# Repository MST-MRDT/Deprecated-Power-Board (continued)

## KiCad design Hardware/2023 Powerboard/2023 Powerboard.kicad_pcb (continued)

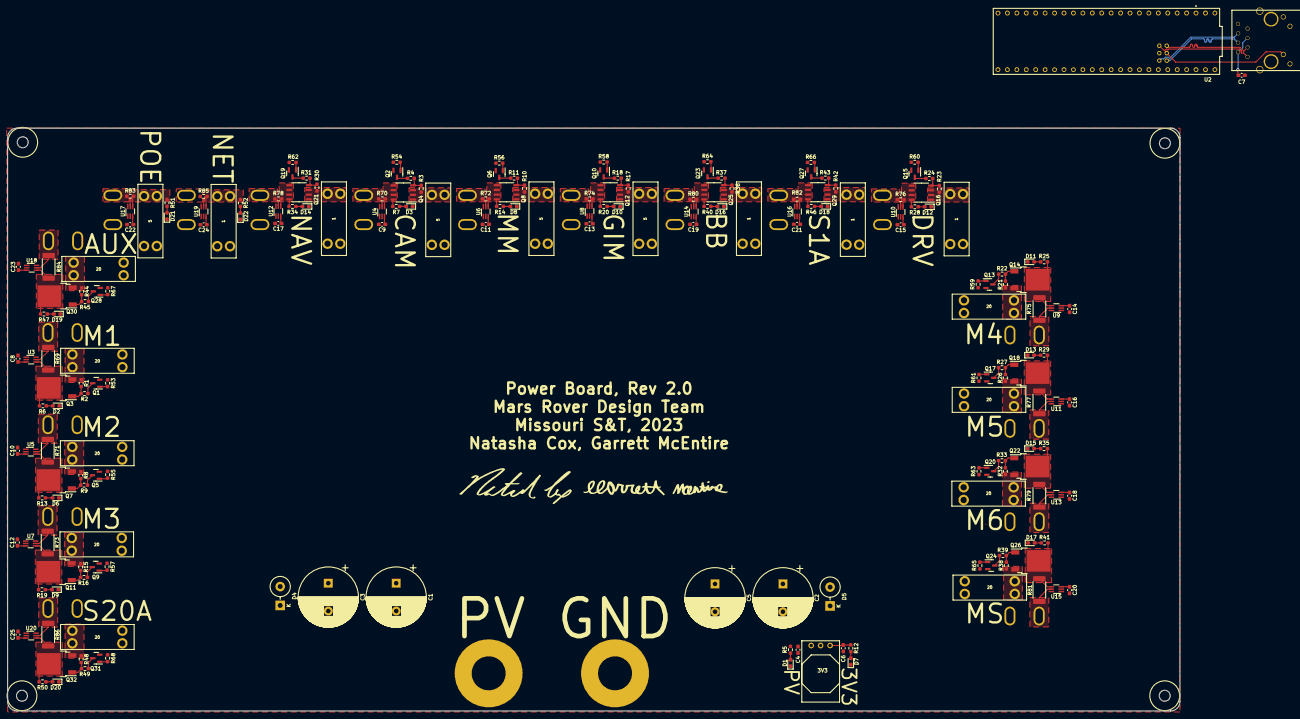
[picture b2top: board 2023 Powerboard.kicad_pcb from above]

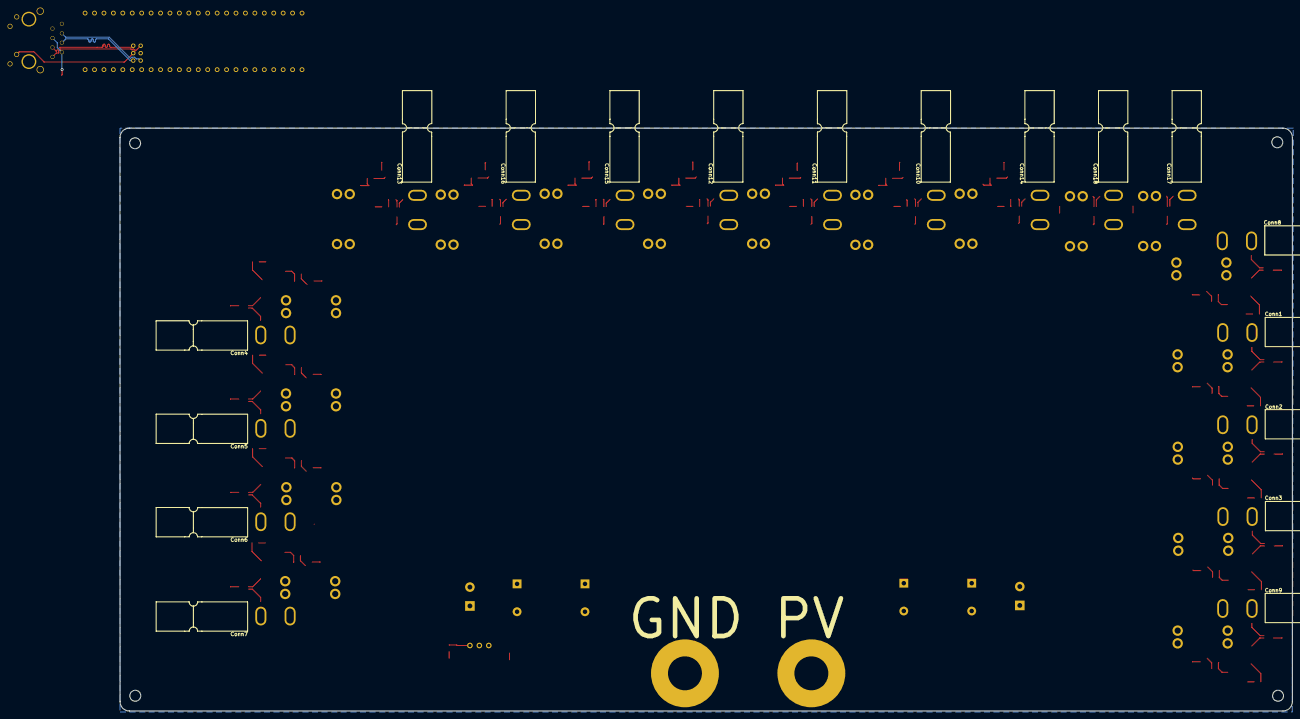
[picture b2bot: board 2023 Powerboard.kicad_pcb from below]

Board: 4 copper layers, 315.7 x 157.0 mm, 228 parts (18 on the bottom side), 147 nets.

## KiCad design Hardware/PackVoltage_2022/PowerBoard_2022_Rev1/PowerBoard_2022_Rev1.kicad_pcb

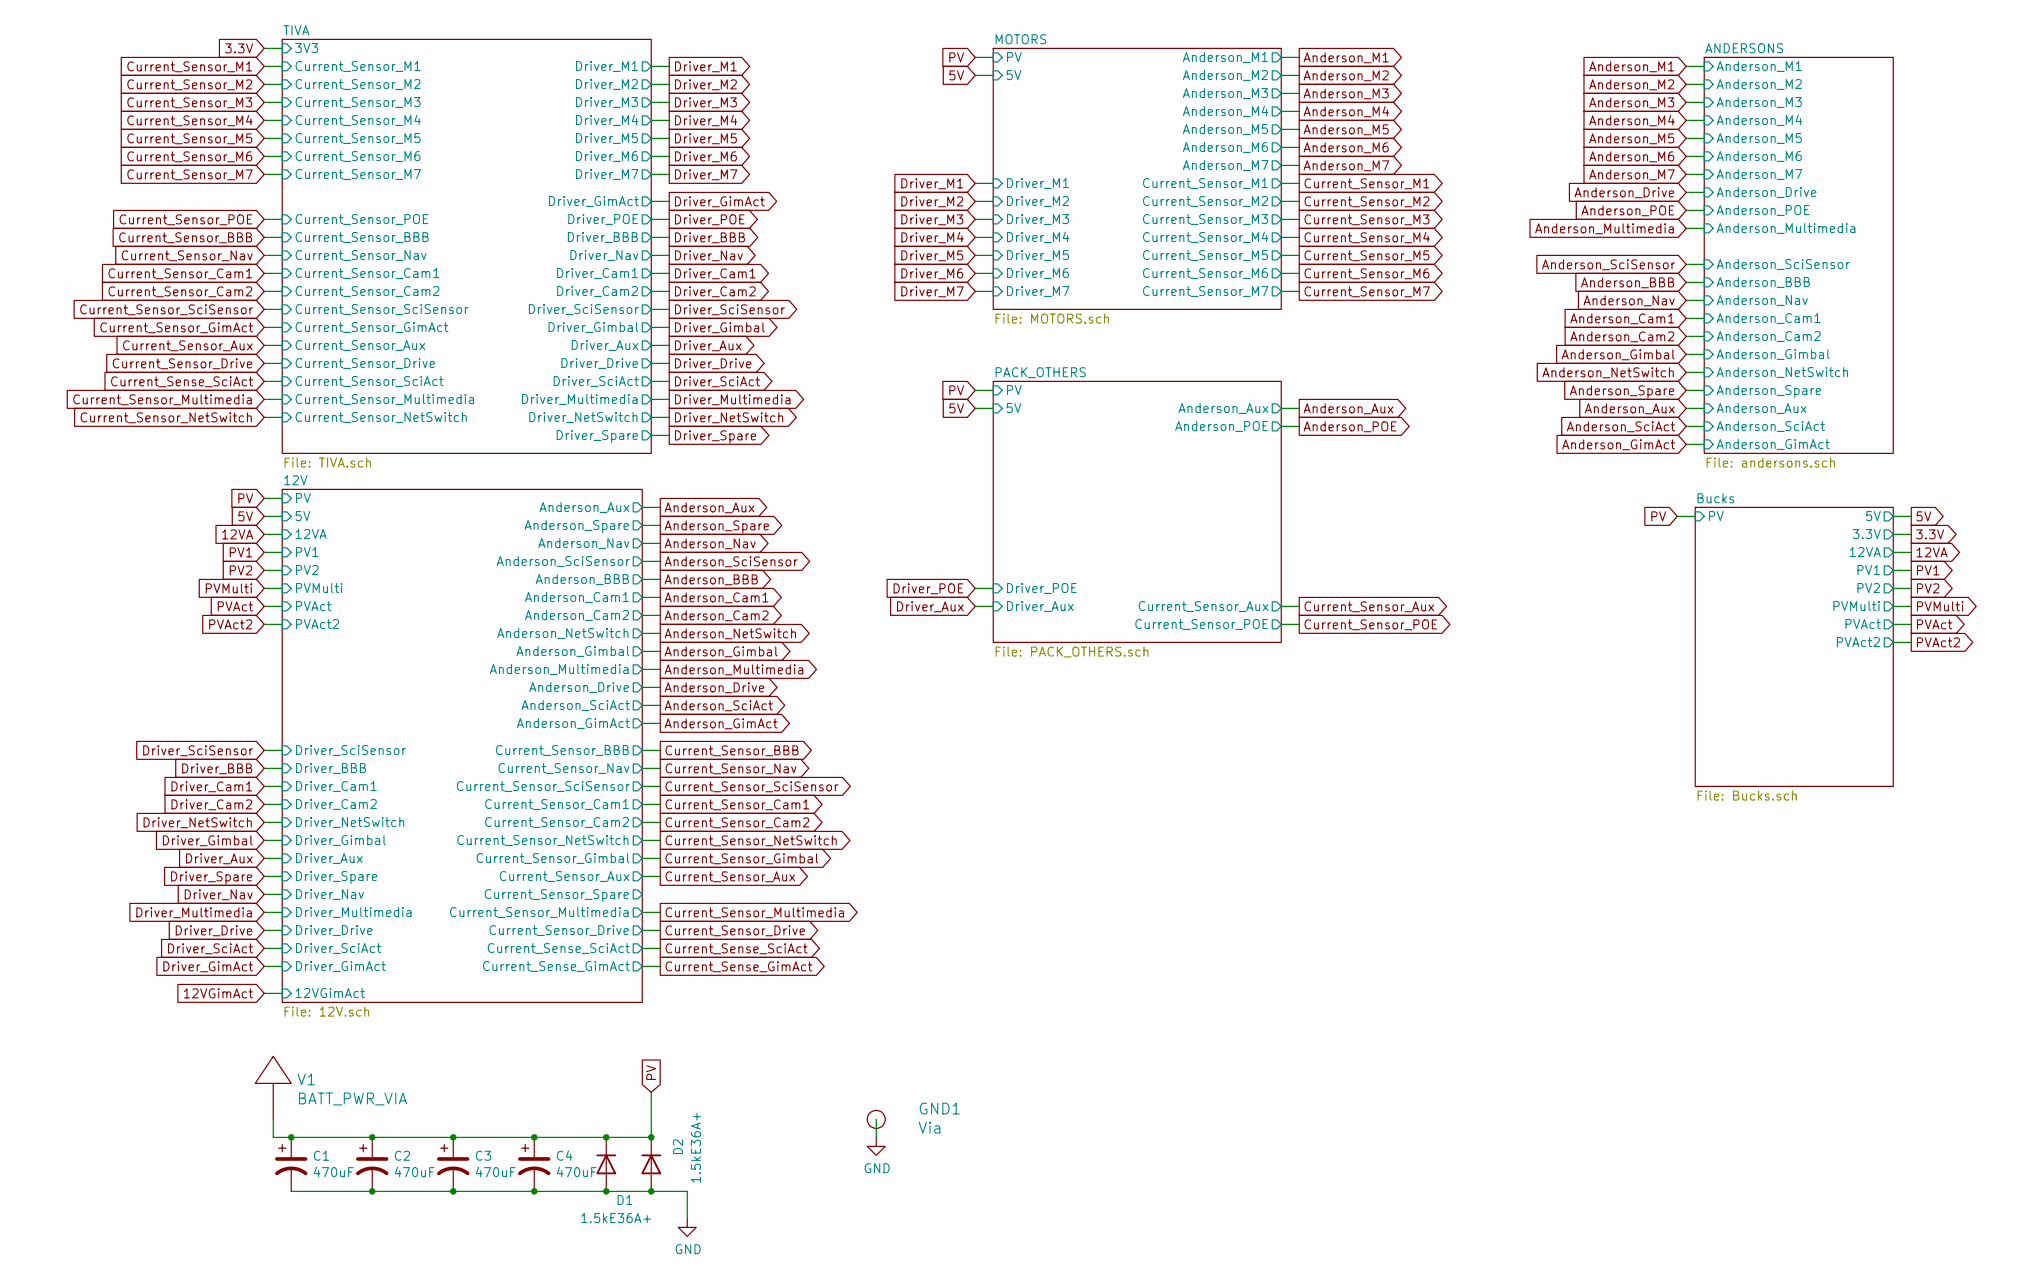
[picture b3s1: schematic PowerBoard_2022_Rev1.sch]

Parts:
C1, C2, C3, C4: 470uF; CP_Radial_D12.5mm_P5.00mm
D1, D2: 1.5kE36A+; D_DO-201_P5.08mm_Vertical_KathodeUp
GND1: Via; BATT_PWR_VIA
V1: BATT_PWR_VIA

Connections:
GND: C1.2, C2.2, C3.2, C4.2, D1.2 (A), D2.2 (A), GND1.1; also elsewhere on the board
PV: C1.1, C2.1, C3.1, C4.1, D1.1 (K), D2.1 (K), V1.1; also elsewhere on the board

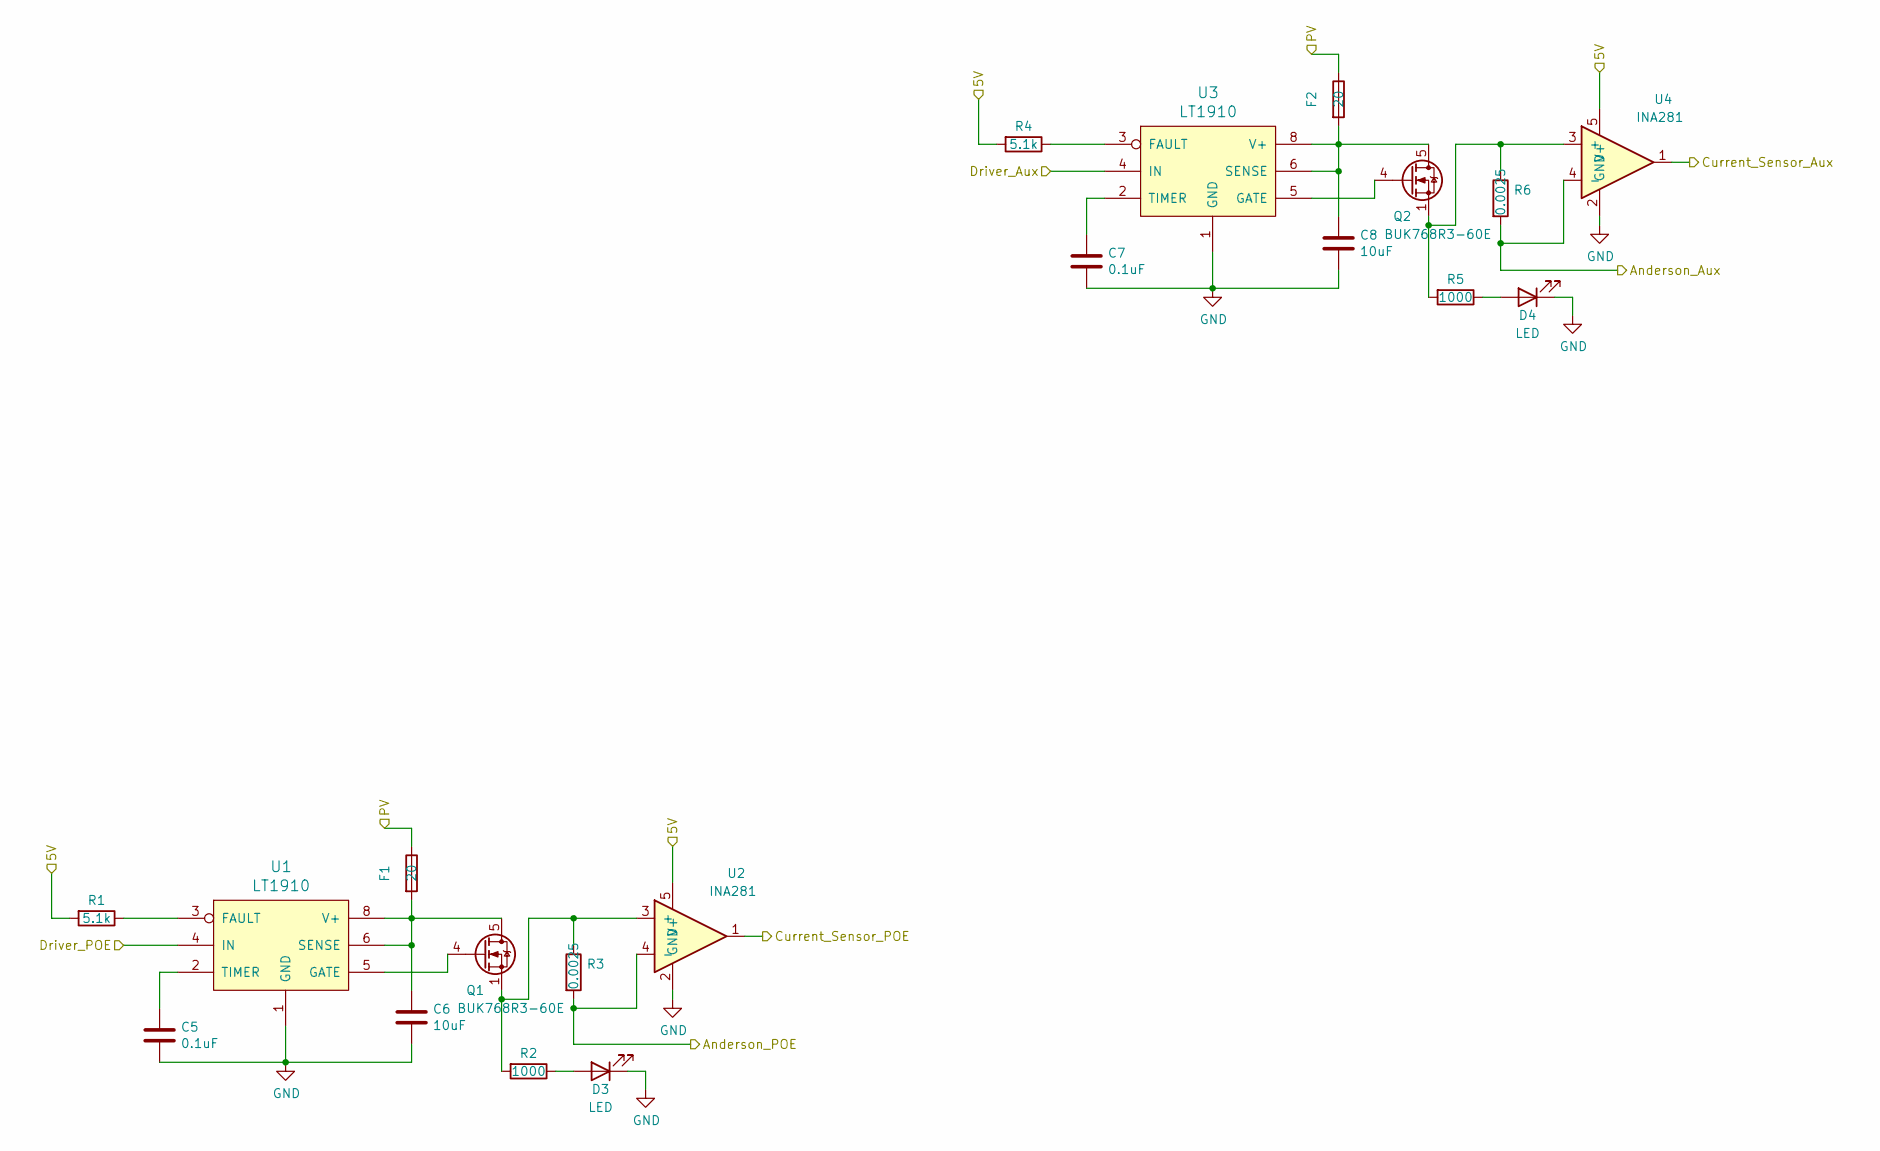
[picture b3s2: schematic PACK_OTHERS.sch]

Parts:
C5, C7: 0.1uF; C_0603_1608Metric_Pad1.05x0.95mm_HandSolder
C6, C8: 10uF; C_0603_1608Metric_Pad1.05x0.95mm_HandSolder
D3, D4: LED; LED_0603_1608Metric_Pad1.05x0.95mm_HandSolder
F1, F2: 20; ATC_Fuse_Block
Q1, Q2: BUK768R3-60E; LFPAK33
R1, R4: 5.1k; R_0603_1608Metric_Pad1.05x0.95mm_HandSolder
R2, R5: 1000; R_0603_1608Metric_Pad1.05x0.95mm_HandSolder
R3, R6: 0.0025; R_0402_1005Metric_Pad0.72x0.64mm_HandSolder
U1, U3: LT1910; SOIC-8_3.9x4.9mm_P1.27mm
U2, U4: INA281; SOT-23-5

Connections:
5V: R1.2, R4.2, U2.5 (V+), U4.5 (V+); also elsewhere on the board
Anderson_Aux: R6.2, U4.4 (-); also elsewhere on the board
Anderson_POE: R3.2, U2.4 (-); also elsewhere on the board
Current_Sensor_Aux: U4.1; also elsewhere on the board
Current_Sensor_POE: U2.1; also elsewhere on the board
Driver_Aux: U3.4 (IN); also elsewhere on the board
Driver_POE: U1.4 (IN); also elsewhere on the board
GND: C5.2, C6.2, C7.2, C8.2, D3.1 (K), D4.1 (K), U1.1 (GND), U2.2 (GND), U3.1 (GND), U4.2 (GND); also elsewhere on the board
unnamed: C5.1, U1.2 (TIMER)
unnamed: C6.1, F1.2, Q1.5 (D), U1.6 (SENSE), U1.8 (V+)
unnamed: C7.1, U3.2 (TIMER)
unnamed: C8.1, F2.2, Q2.5 (D), U3.6 (SENSE), U3.8 (V+)
unnamed: D3.2 (A), R2.1
unnamed: D4.2 (A), R5.1
unnamed: Q1.1 (S), Q1.2 (S), Q1.3 (S), R2.2, R3.1, U2.3 (+)
unnamed: Q1.4 (G), U1.5 (GATE)
unnamed: Q2.1 (S), Q2.2 (S), Q2.3 (S), R5.2, R6.1, U4.3 (+)
unnamed: Q2.4 (G), U3.5 (GATE)
unnamed: R1.1, U1.3 (FAULT)
unnamed: R4.1, U3.3 (FAULT)
PV: F1.1, F2.1; also elsewhere on the board

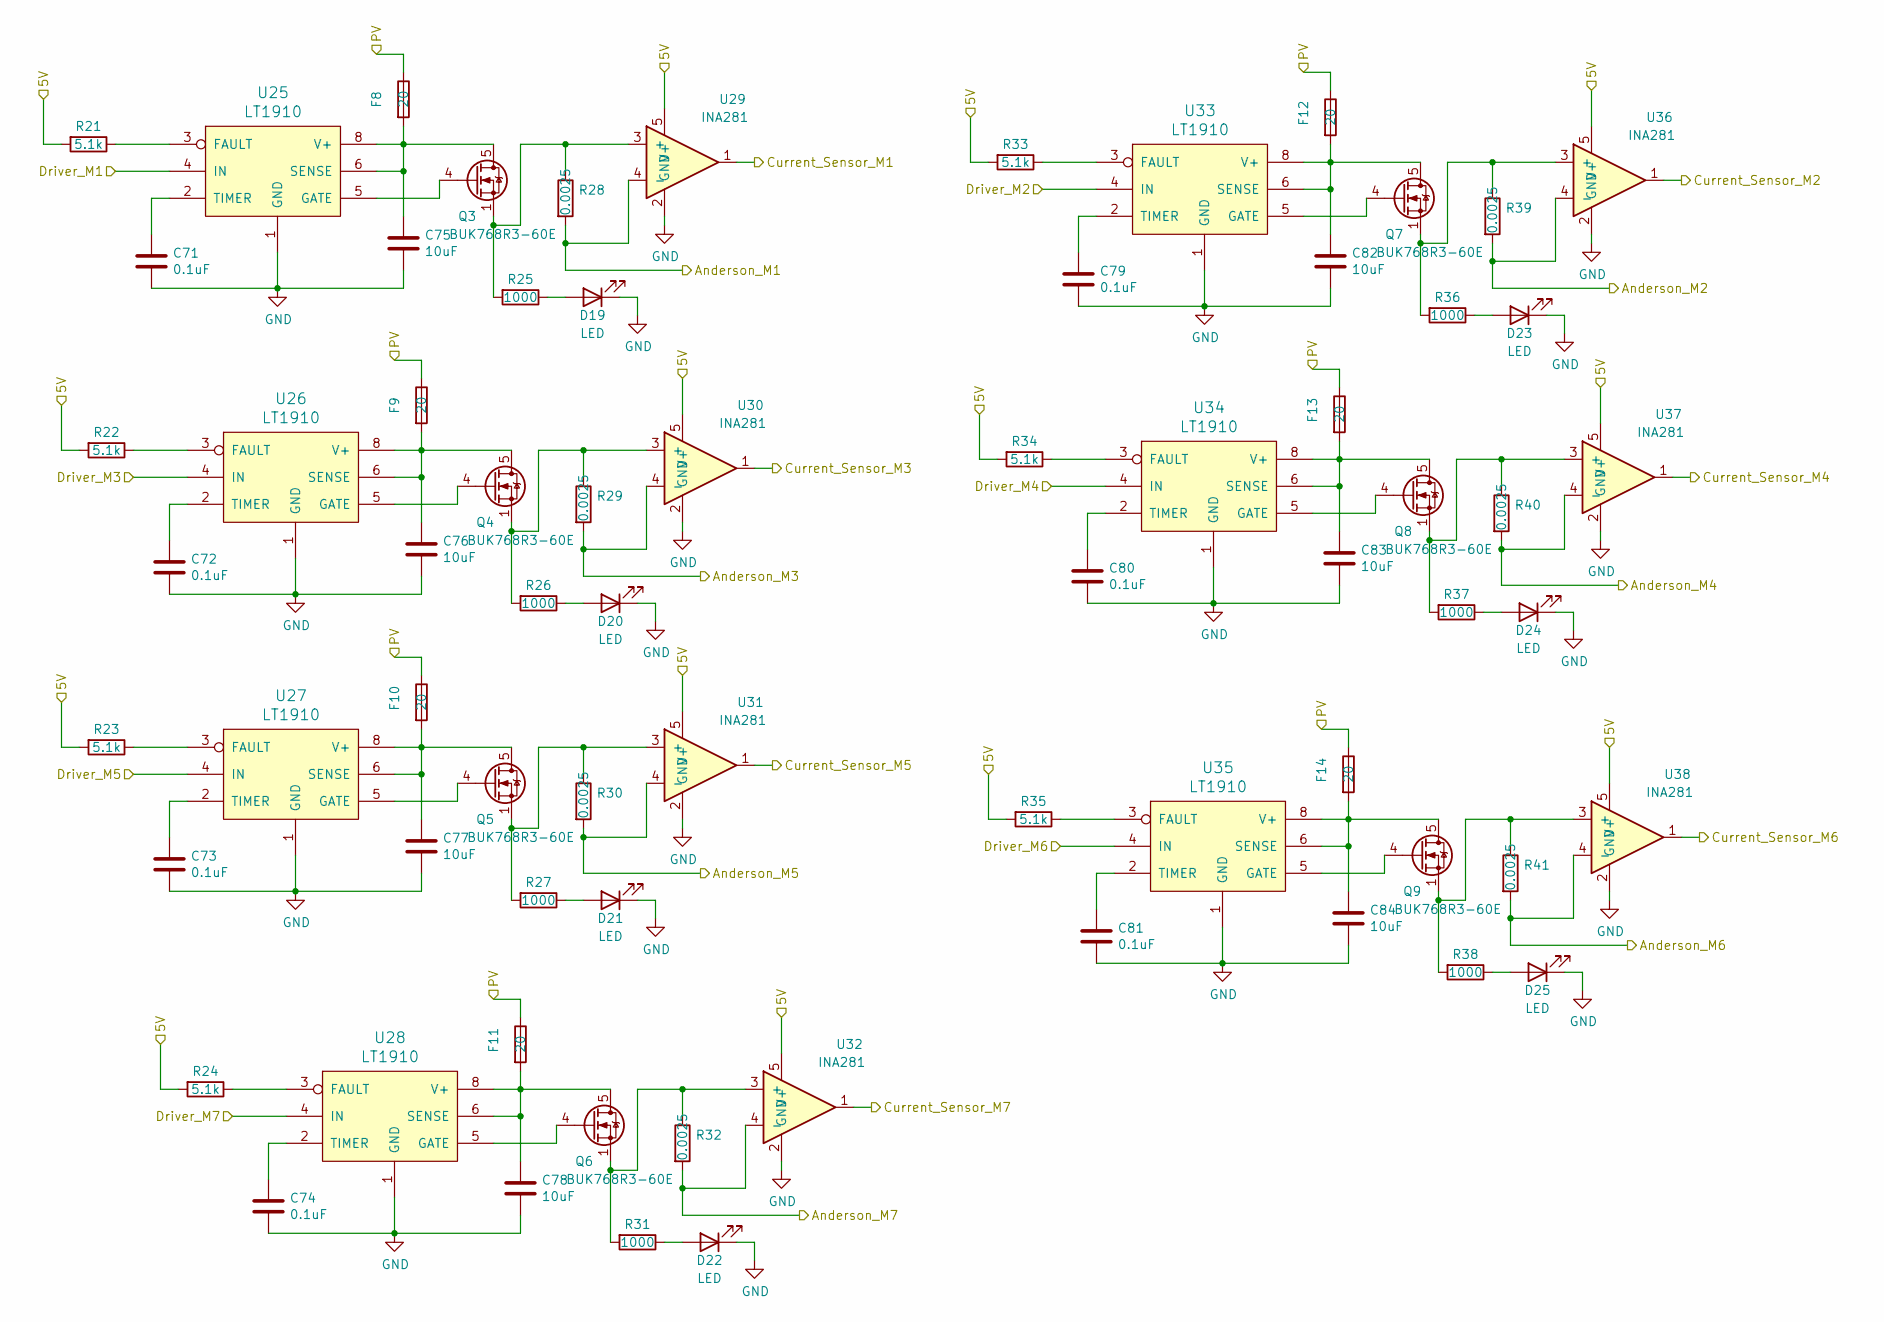
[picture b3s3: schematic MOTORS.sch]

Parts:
C71, C72, C73, C74, C79, C80, C81: 0.1uF; C_0603_1608Metric_Pad1.05x0.95mm_HandSolder
C75, C76, C77, C78, C82, C83, C84: 10uF; C_0603_1608Metric_Pad1.05x0.95mm_HandSolder
D19, D20, D21, D22, D23, D24, D25: LED; LED_0603_1608Metric_Pad1.05x0.95mm_HandSolder
F8, F9, F10, F11, F12, F13, F14: 20; ATC_Fuse_Block
Q3, Q4, Q5, Q6, Q7, Q8, Q9: BUK768R3-60E; LFPAK33
R21, R22, R23, R24, R33, R34, R35: 5.1k; R_0603_1608Metric_Pad1.05x0.95mm_HandSolder
R25, R26, R27, R31, R36, R37, R38: 1000; R_0603_1608Metric_Pad1.05x0.95mm_HandSolder
R28, R29, R30, R32, R39, R40, R41: 0.0025; R_0402_1005Metric_Pad0.72x0.64mm_HandSolder
U25, U26, U27, U28, U33, U34, U35: LT1910; SOIC-8_3.9x4.9mm_P1.27mm
U29, U30, U31, U32, U36, U37, U38: INA281; SOT-23-5

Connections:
5V: R21.2, R22.2, R23.2, R24.2, R33.2, R34.2, R35.2, U29.5 (V+), U30.5 (V+), U31.5 (V+), U32.5 (V+), U36.5 (V+), U37.5 (V+), U38.5 (V+); also elsewhere on the board
Anderson_M1: R28.2, U29.4 (-); also elsewhere on the board
Anderson_M2: R39.2, U36.4 (-); also elsewhere on the board
Anderson_M3: R29.2, U30.4 (-); also elsewhere on the board
Anderson_M4: R40.2, U37.4 (-); also elsewhere on the board
Anderson_M5: R30.2, U31.4 (-); also elsewhere on the board
Anderson_M6: R41.2, U38.4 (-); also elsewhere on the board
Anderson_M7: R32.2, U32.4 (-); also elsewhere on the board
Current_Sensor_M1: U29.1; also elsewhere on the board
Current_Sensor_M2: U36.1; also elsewhere on the board
Current_Sensor_M3: U30.1; also elsewhere on the board
Current_Sensor_M4: U37.1; also elsewhere on the board
Current_Sensor_M5: U31.1; also elsewhere on the board
Current_Sensor_M6: U38.1; also elsewhere on the board
Current_Sensor_M7: U32.1; also elsewhere on the board
Driver_M1: U25.4 (IN); also elsewhere on the board
Driver_M2: U33.4 (IN); also elsewhere on the board
Driver_M3: U26.4 (IN); also elsewhere on the board
Driver_M4: U34.4 (IN); also elsewhere on the board
Driver_M5: U27.4 (IN); also elsewhere on the board
Driver_M6: U35.4 (IN); also elsewhere on the board
Driver_M7: U28.4 (IN); also elsewhere on the board
GND: C71.2, C72.2, C73.2, C74.2, C75.2, C76.2, C77.2, C78.2, C79.2, C80.2, C81.2, C82.2, C83.2, C84.2, D19.1 (K), D20.1 (K), D21.1 (K), D22.1 (K), D23.1 (K), D24.1 (K), D25.1 (K), U25.1 (GND), U26.1 (GND), U27.1 (GND), U28.1 (GND), U29.2 (GND), U30.2 (GND), U31.2 (GND), U32.2 (GND), U33.1 (GND), U34.1 (GND), U35.1 (GND), U36.2 (GND), U37.2 (GND), U38.2 (GND); also elsewhere on the board
unnamed: C71.1, U25.2 (TIMER)
unnamed: C72.1, U26.2 (TIMER)
unnamed: C73.1, U27.2 (TIMER)
unnamed: C74.1, U28.2 (TIMER)
unnamed: C75.1, F8.2, Q3.5 (D), U25.6 (SENSE), U25.8 (V+)
unnamed: C76.1, F9.2, Q4.5 (D), U26.6 (SENSE), U26.8 (V+)
unnamed: C77.1, F10.2, Q5.5 (D), U27.6 (SENSE), U27.8 (V+)
unnamed: C78.1, F11.2, Q6.5 (D), U28.6 (SENSE), U28.8 (V+)
unnamed: C79.1, U33.2 (TIMER)
unnamed: C80.1, U34.2 (TIMER)
unnamed: C81.1, U35.2 (TIMER)
unnamed: C82.1, F12.2, Q7.5 (D), U33.6 (SENSE), U33.8 (V+)
unnamed: C83.1, F13.2, Q8.5 (D), U34.6 (SENSE), U34.8 (V+)
unnamed: C84.1, F14.2, Q9.5 (D), U35.6 (SENSE), U35.8 (V+)
unnamed: D19.2 (A), R25.1
unnamed: D20.2 (A), R26.1
unnamed: D21.2 (A), R27.1
unnamed: D22.2 (A), R31.1
unnamed: D23.2 (A), R36.1
unnamed: D24.2 (A), R37.1
unnamed: D25.2 (A), R38.1
unnamed: Q3.1 (S), Q3.2 (S), Q3.3 (S), R25.2, R28.1, U29.3 (+)
unnamed: Q3.4 (G), U25.5 (GATE)
unnamed: Q4.1 (S), Q4.2 (S), Q4.3 (S), R26.2, R29.1, U30.3 (+)
unnamed: Q4.4 (G), U26.5 (GATE)
unnamed: Q5.1 (S), Q5.2 (S), Q5.3 (S), R27.2, R30.1, U31.3 (+)
unnamed: Q5.4 (G), U27.5 (GATE)
unnamed: Q6.1 (S), Q6.2 (S), Q6.3 (S), R31.2, R32.1, U32.3 (+)
unnamed: Q6.4 (G), U28.5 (GATE)
unnamed: Q7.1 (S), Q7.2 (S), Q7.3 (S), R36.2, R39.1, U36.3 (+)
unnamed: Q7.4 (G), U33.5 (GATE)
unnamed: Q8.1 (S), Q8.2 (S), Q8.3 (S), R37.2, R40.1, U37.3 (+)
unnamed: Q8.4 (G), U34.5 (GATE)
unnamed: Q9.1 (S), Q9.2 (S), Q9.3 (S), R38.2, R41.1, U38.3 (+)
unnamed: Q9.4 (G), U35.5 (GATE)
unnamed: R21.1, U25.3 (FAULT)
unnamed: R22.1, U26.3 (FAULT)
unnamed: R23.1, U27.3 (FAULT)
unnamed: R24.1, U28.3 (FAULT)
unnamed: R33.1, U33.3 (FAULT)
unnamed: R34.1, U34.3 (FAULT)
unnamed: R35.1, U35.3 (FAULT)
PV: F8.1, F9.1, F10.1, F11.1, F12.1, F13.1, F14.1; also elsewhere on the board

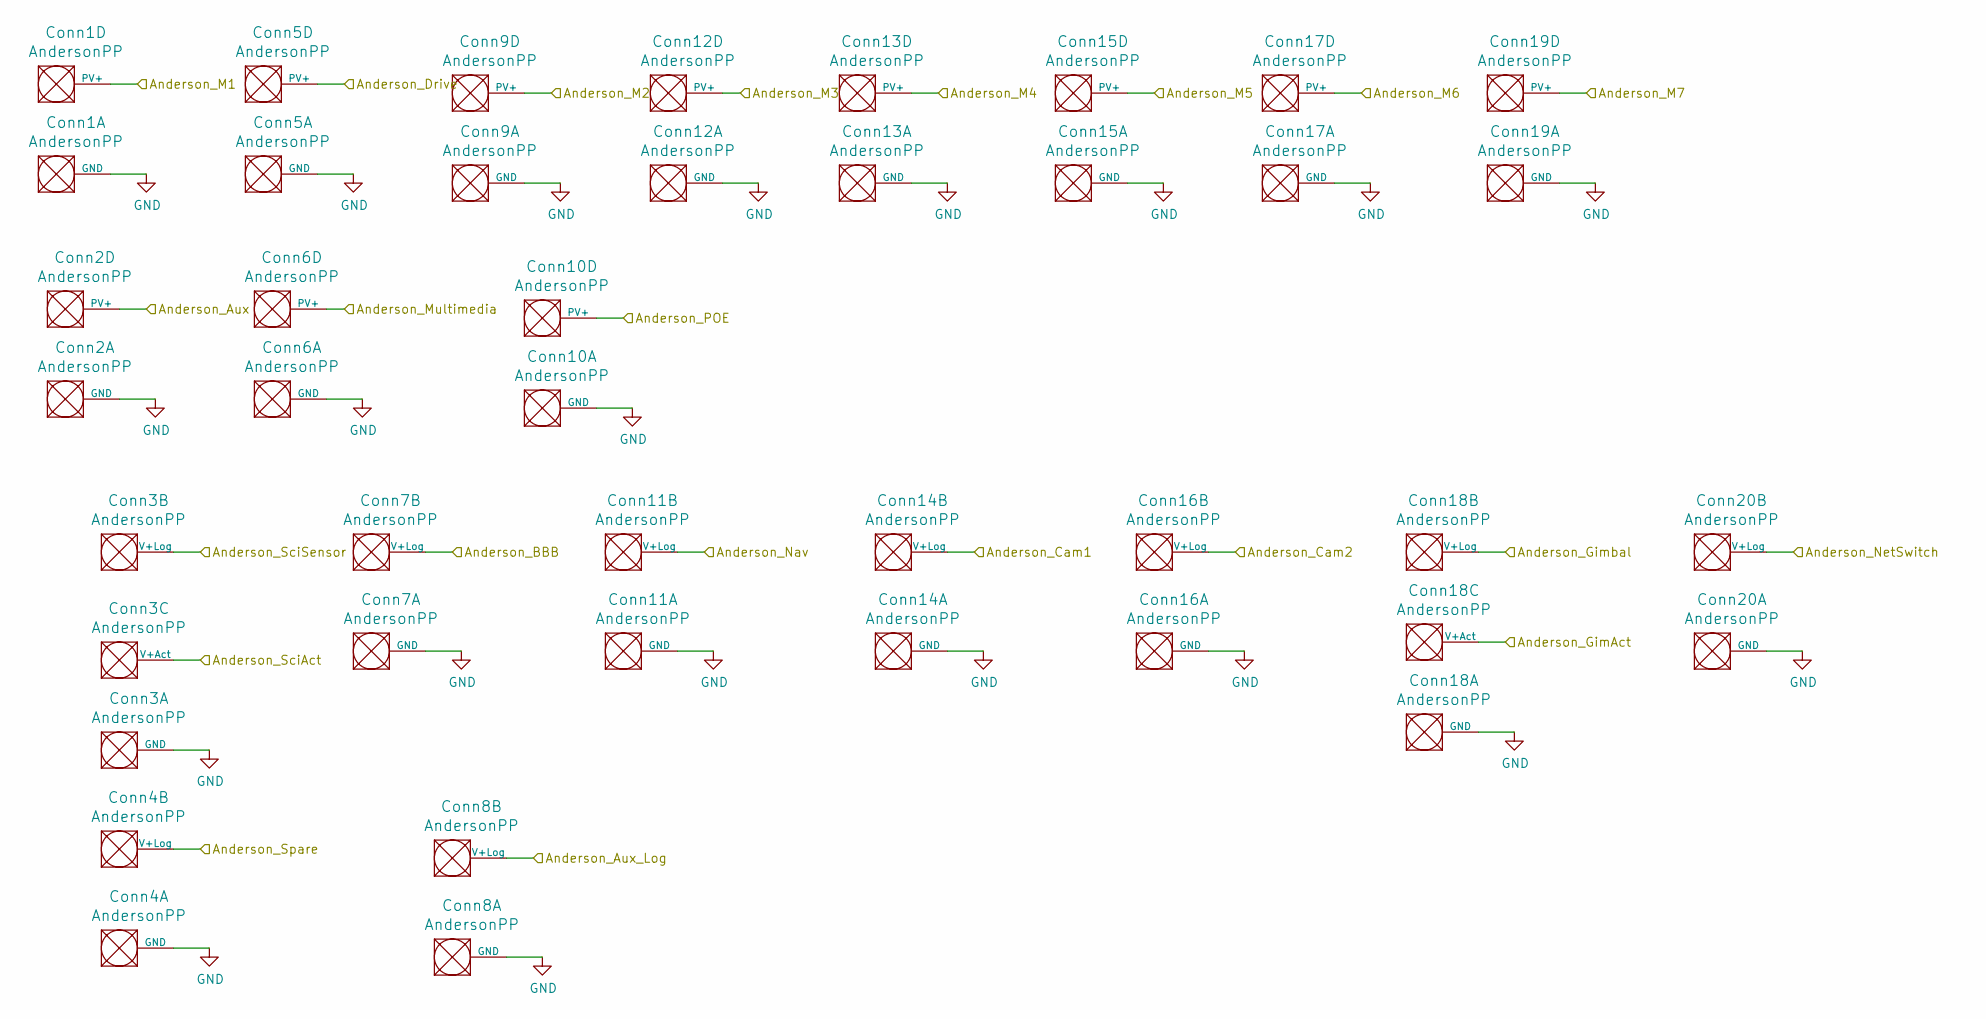
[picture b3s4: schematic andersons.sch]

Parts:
Conn1, Conn2, Conn5, Conn6, Conn9, Conn10, Conn12, Conn13, Conn15, Conn17, Conn19: AndersonPP; Anderson_2_Vertical_Side_by_Side_PV
Conn3, Conn18: AndersonPP; Anderson_3_Vertical_Side_by_Side
Conn4, Conn7, Conn8, Conn11, Conn14, Conn16, Conn20: AndersonPP; Anderson_2_Vertical_Sidy_by_Side

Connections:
Anderson_Aux: Conn2.4 (PV+); also elsewhere on the board
Anderson_Aux_Logic: Conn8.2 (V+Log); also elsewhere on the board
Anderson_BBB: Conn7.2 (V+Log); also elsewhere on the board
Anderson_Cam1: Conn14.2 (V+Log); also elsewhere on the board
Anderson_Cam2: Conn16.2 (V+Log); also elsewhere on the board
Anderson_Drive: Conn5.4 (PV+); also elsewhere on the board
Anderson_GimAct: Conn18.3 (V+Act); also elsewhere on the board
Anderson_Gimbal: Conn18.2 (V+Log); also elsewhere on the board
Anderson_M1: Conn1.4 (PV+); also elsewhere on the board
Anderson_M2: Conn9.4 (PV+); also elsewhere on the board
Anderson_M3: Conn12.4 (PV+); also elsewhere on the board
Anderson_M4: Conn13.4 (PV+); also elsewhere on the board
Anderson_M5: Conn15.4 (PV+); also elsewhere on the board
Anderson_M6: Conn17.4 (PV+); also elsewhere on the board
Anderson_M7: Conn19.4 (PV+); also elsewhere on the board
Anderson_Multimedia: Conn6.4 (PV+); also elsewhere on the board
Anderson_Nav: Conn11.2 (V+Log); also elsewhere on the board
Anderson_NetSwitch: Conn20.2 (V+Log); also elsewhere on the board
Anderson_POE: Conn10.4 (PV+); also elsewhere on the board
Anderson_SciAct: Conn3.3 (V+Act); also elsewhere on the board
Anderson_SciSensor: Conn3.2 (V+Log); also elsewhere on the board
Anderson_Spare: Conn4.2 (V+Log); also elsewhere on the board
GND: Conn1.1 (GND), Conn2.1 (GND), Conn3.1 (GND), Conn4.1 (GND), Conn5.1 (GND), Conn6.1 (GND), Conn7.1 (GND), Conn8.1 (GND), Conn9.1 (GND), Conn10.1 (GND), Conn11.1 (GND), Conn12.1 (GND), Conn13.1 (GND), Conn14.1 (GND), Conn15.1 (GND), Conn16.1 (GND), Conn17.1 (GND), Conn18.1 (GND), Conn19.1 (GND), Conn20.1 (GND); also elsewhere on the board

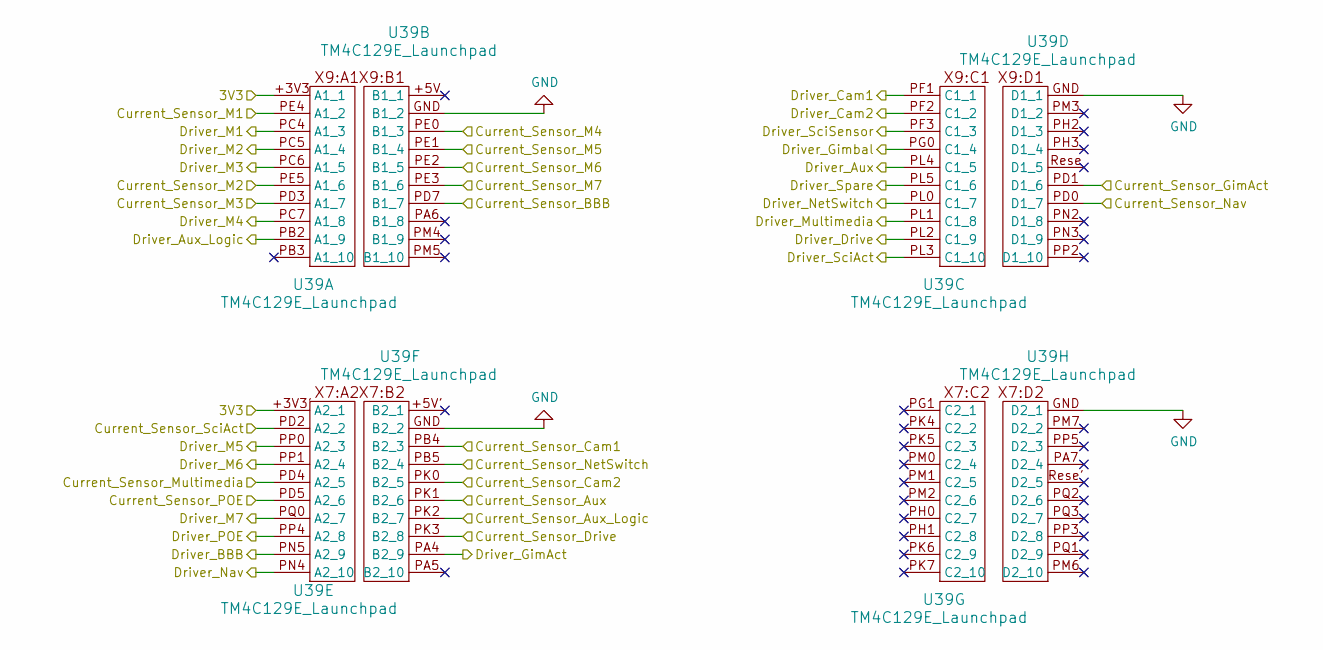
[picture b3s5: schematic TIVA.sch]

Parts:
U39: TM4C129E_Launchpad; TM4C129E_Launchpad_FULL_THT_TOP

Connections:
3.3V: U39.+3V3 (A1_1), U39.+3V3' (A2_1); also elsewhere on the board
Current_Sensor_Aux: U39.PK1 (B2_6); also elsewhere on the board
Current_Sensor_Aux_Logic: U39.PK2 (B2_7); also elsewhere on the board
Current_Sensor_BBB: U39.PD7 (B1_7); also elsewhere on the board
Current_Sensor_Cam1: U39.PB4 (B2_3); also elsewhere on the board
Current_Sensor_Cam2: U39.PK0 (B2_5); also elsewhere on the board
Current_Sensor_Drive: U39.PK3 (B2_8); also elsewhere on the board
Current_Sensor_GimAct: U39.PD1 (D1_6); also elsewhere on the board
Current_Sensor_M1: U39.PE4 (A1_2); also elsewhere on the board
Current_Sensor_M2: U39.PE5 (A1_6); also elsewhere on the board
Current_Sensor_M3: U39.PD3 (A1_7); also elsewhere on the board
Current_Sensor_M4: U39.PE0 (B1_3); also elsewhere on the board
Current_Sensor_M5: U39.PE1 (B1_4); also elsewhere on the board
Current_Sensor_M6: U39.PE2 (B1_5); also elsewhere on the board
Current_Sensor_M7: U39.PE3 (B1_6); also elsewhere on the board
Current_Sensor_Multimedia: U39.PD4 (A2_5); also elsewhere on the board
Current_Sensor_Nav: U39.PD0 (D1_7); also elsewhere on the board
Current_Sensor_NetSwitch: U39.PB5 (B2_4); also elsewhere on the board
Current_Sensor_POE: U39.PD5 (A2_6); also elsewhere on the board
Current_Sensor_SciAct: U39.PD2 (A2_2); also elsewhere on the board
Driver_Aux: U39.PL4 (C1_5); also elsewhere on the board
Driver_Aux_Logic: U39.PB2 (A1_9); also elsewhere on the board
Driver_BBB: U39.PN5 (A2_9); also elsewhere on the board
Driver_Cam1: U39.PF1 (C1_1); also elsewhere on the board
Driver_Cam2: U39.PF2 (C1_2); also elsewhere on the board
Driver_Drive: U39.PL2 (C1_9); also elsewhere on the board
Driver_GimAct: U39.PA4 (B2_9); also elsewhere on the board
Driver_Gimbal: U39.PG0 (C1_4); also elsewhere on the board
Driver_M1: U39.PC4 (A1_3); also elsewhere on the board
Driver_M2: U39.PC5 (A1_4); also elsewhere on the board
Driver_M3: U39.PC6 (A1_5); also elsewhere on the board
Driver_M4: U39.PC7 (A1_8); also elsewhere on the board
Driver_M5: U39.PP0 (A2_3); also elsewhere on the board
Driver_M6: U39.PP1 (A2_4); also elsewhere on the board
Driver_M7: U39.PQ0 (A2_7); also elsewhere on the board
Driver_Multimedia: U39.PL1 (C1_8); also elsewhere on the board
Driver_Nav: U39.PN4 (A2_10); also elsewhere on the board
Driver_NetSwitch: U39.PL0 (C1_7); also elsewhere on the board
Driver_POE: U39.PP4 (A2_8); also elsewhere on the board
Driver_SciAct: U39.PL3 (C1_10); also elsewhere on the board
Driver_SciSensor: U39.PF3 (C1_3); also elsewhere on the board
Driver_Spare: U39.PL5 (C1_6); also elsewhere on the board
GND: U39.GND (B1_2); also elsewhere on the board

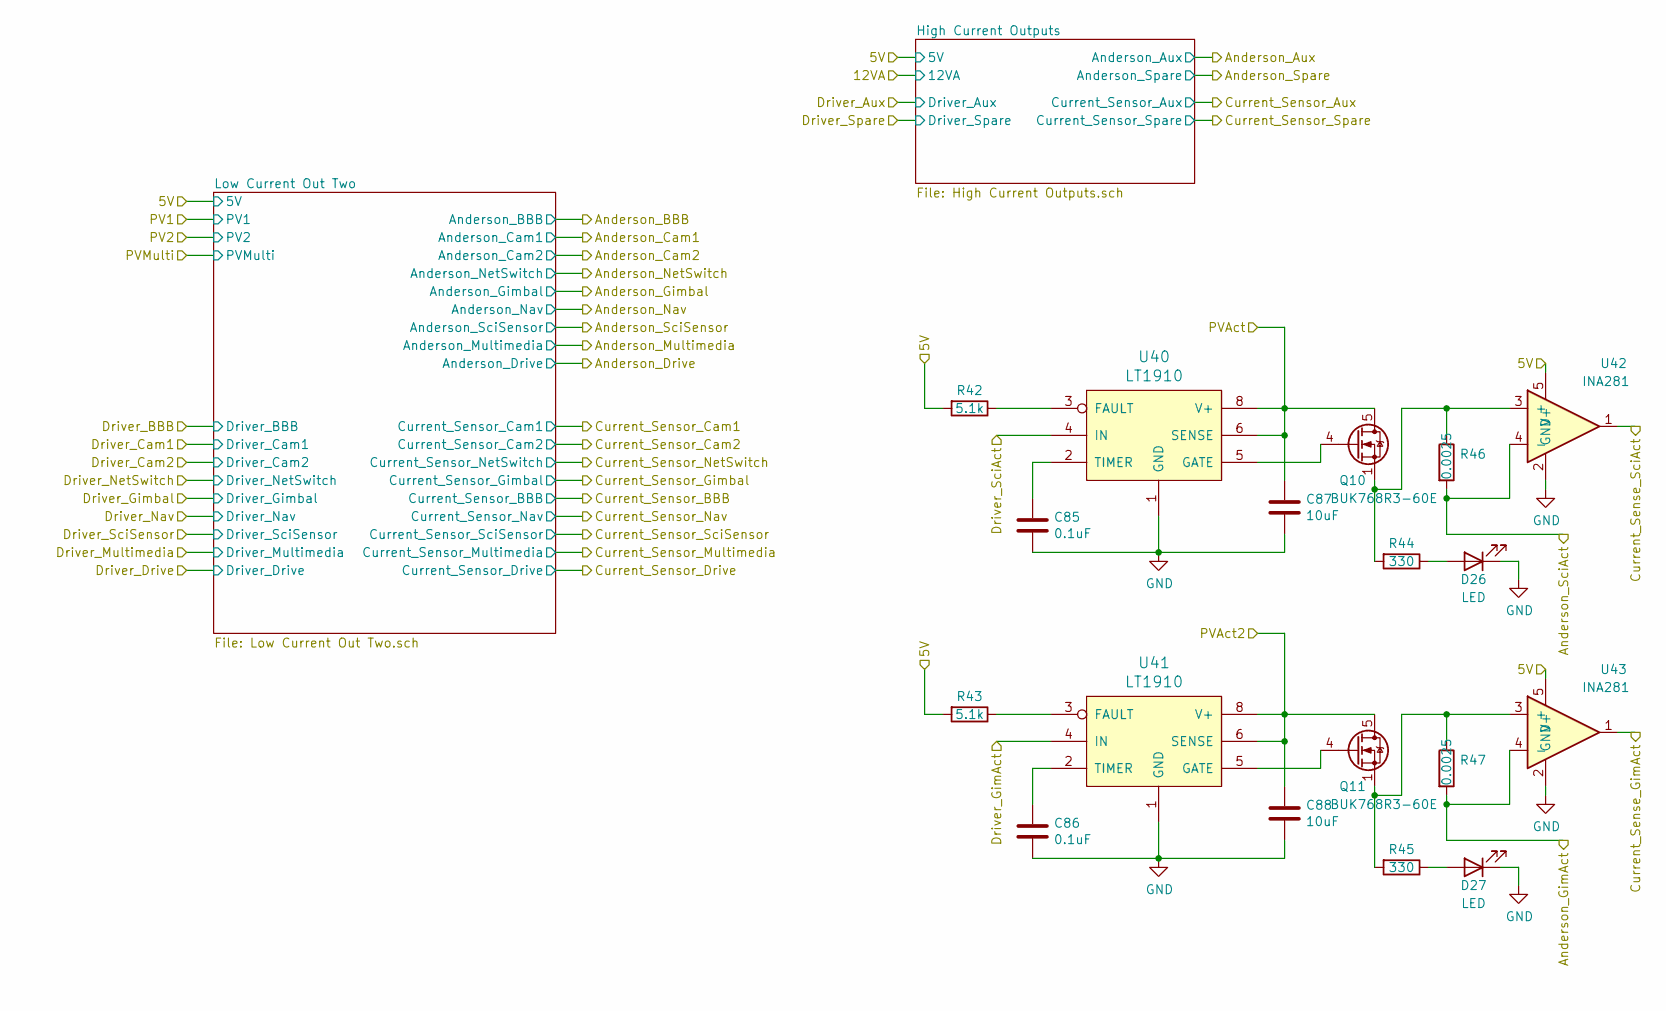
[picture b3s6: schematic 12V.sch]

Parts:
C85, C86: 0.1uF; C_0603_1608Metric_Pad1.05x0.95mm_HandSolder
C87, C88: 10uF; C_0603_1608Metric_Pad1.05x0.95mm_HandSolder
D26, D27: LED; LED_0603_1608Metric_Pad1.05x0.95mm_HandSolder
Q10, Q11: BUK768R3-60E; LFPAK33
R42, R43: 5.1k; R_0603_1608Metric_Pad1.05x0.95mm_HandSolder
R44, R45: 330; R_0603_1608Metric_Pad1.05x0.95mm_HandSolder
R46, R47: 0.0025; R_0402_1005Metric_Pad0.72x0.64mm_HandSolder
U40, U41: LT1910; SOIC-8_3.9x4.9mm_P1.27mm
U42, U43: INA281; SOT-23-5

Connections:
5V: R42.2, R43.2, U42.5 (V+), U43.5 (V+); also elsewhere on the board
Anderson_GimAct: R47.2, U43.4 (-); also elsewhere on the board
Anderson_SciAct: R46.2, U42.4 (-); also elsewhere on the board
Current_Sensor_GimAct: U43.1; also elsewhere on the board
Current_Sensor_SciAct: U42.1; also elsewhere on the board
Driver_GimAct: U41.4 (IN); also elsewhere on the board
Driver_SciAct: U40.4 (IN); also elsewhere on the board
GND: C85.2, C86.2, C87.2, C88.2, D26.1 (K), D27.1 (K), U40.1 (GND), U41.1 (GND), U42.2 (GND), U43.2 (GND); also elsewhere on the board
unnamed: C85.1, U40.2 (TIMER)
unnamed: C86.1, U41.2 (TIMER)
unnamed: D26.2 (A), R44.1
unnamed: D27.2 (A), R45.1
unnamed: Q10.1 (S), Q10.2 (S), Q10.3 (S), R44.2, R46.1, U42.3 (+)
unnamed: Q10.4 (G), U40.5 (GATE)
unnamed: Q11.1 (S), Q11.2 (S), Q11.3 (S), R45.2, R47.1, U43.3 (+)
unnamed: Q11.4 (G), U41.5 (GATE)
unnamed: R42.1, U40.3 (FAULT)
unnamed: R43.1, U41.3 (FAULT)
PVAct: C87.1, Q10.5 (D), U40.6 (SENSE), U40.8 (V+); also elsewhere on the board
PVAct2: C88.1, Q11.5 (D), U41.6 (SENSE), U41.8 (V+); also elsewhere on the board
